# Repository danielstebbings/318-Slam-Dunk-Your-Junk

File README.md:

# SLAM DUNK YOUR JUNK!

This is the full repository for slam dunk your junk, including PCB design files and all source code.

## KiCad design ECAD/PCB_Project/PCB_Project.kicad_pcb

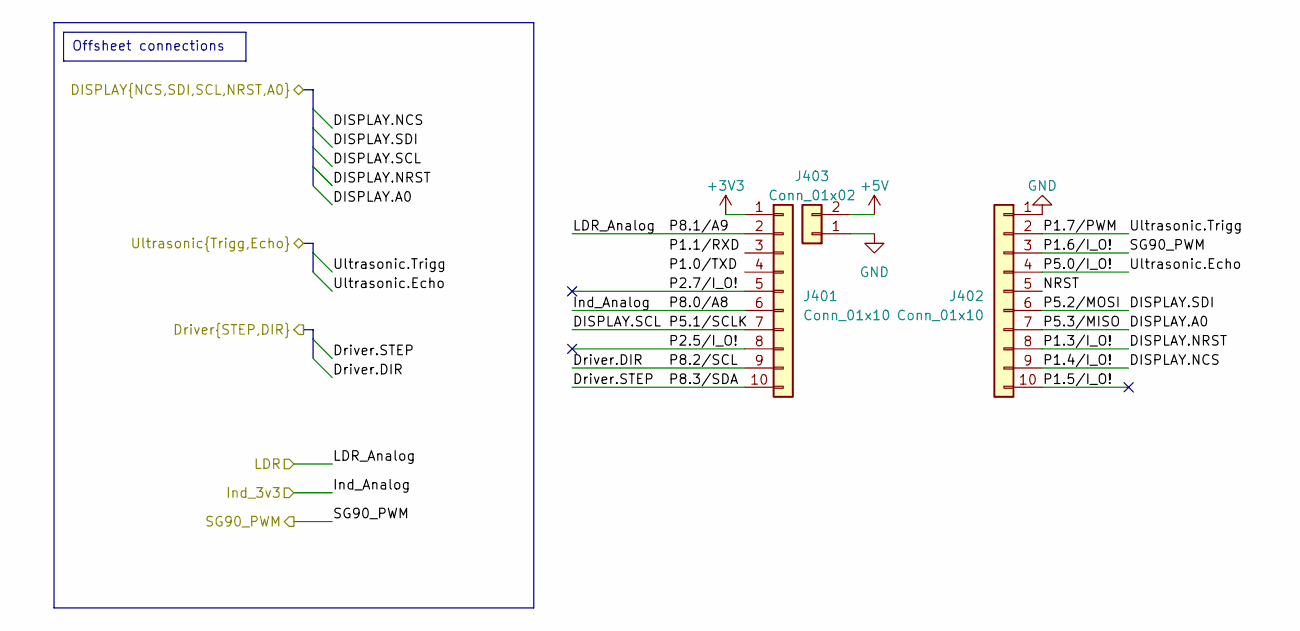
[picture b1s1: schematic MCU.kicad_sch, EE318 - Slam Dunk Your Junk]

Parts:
J401, J402: Conn_01x10; PinSocket_1x10_P2.54mm_Vertical
J403: Conn_01x02; PinHeader_1x02_P2.54mm_Vertical

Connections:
+3V3: J401.1; also elsewhere on the board
+5V: J403.2; also elsewhere on the board
/Display/DISPLAY.A0: J402.7; also elsewhere on the board
/Display/DISPLAY.NCS: J402.9; also elsewhere on the board
/Display/DISPLAY.NRST: J402.8; also elsewhere on the board
/Display/DISPLAY.SCL: J401.7; also elsewhere on the board
/Display/DISPLAY.SDI: J402.6; also elsewhere on the board
/MCU/Driver.DIR: J401.9; also elsewhere on the board
/MCU/Driver.STEP: J401.10; also elsewhere on the board
/MCU/Ind_Analog: J401.6; also elsewhere on the board
/MCU/LDR_Analog: J401.2; also elsewhere on the board
/MCU/NRST: J402.5
/MCU/P1.5/I_O!: J402.10
/MCU/P1.6/I_O!: J402.3; also elsewhere on the board
/MCU/P2.5/I_O!: J401.8
/MCU/P2.7/I_O!: J401.5
/MCU/Ultrasonic.Echo: J402.4; also elsewhere on the board
/MCU/Ultrasonic.Trigg: J402.2; also elsewhere on the board
GND: J402.1, J403.1; also elsewhere on the board

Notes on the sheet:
Offsheet connections

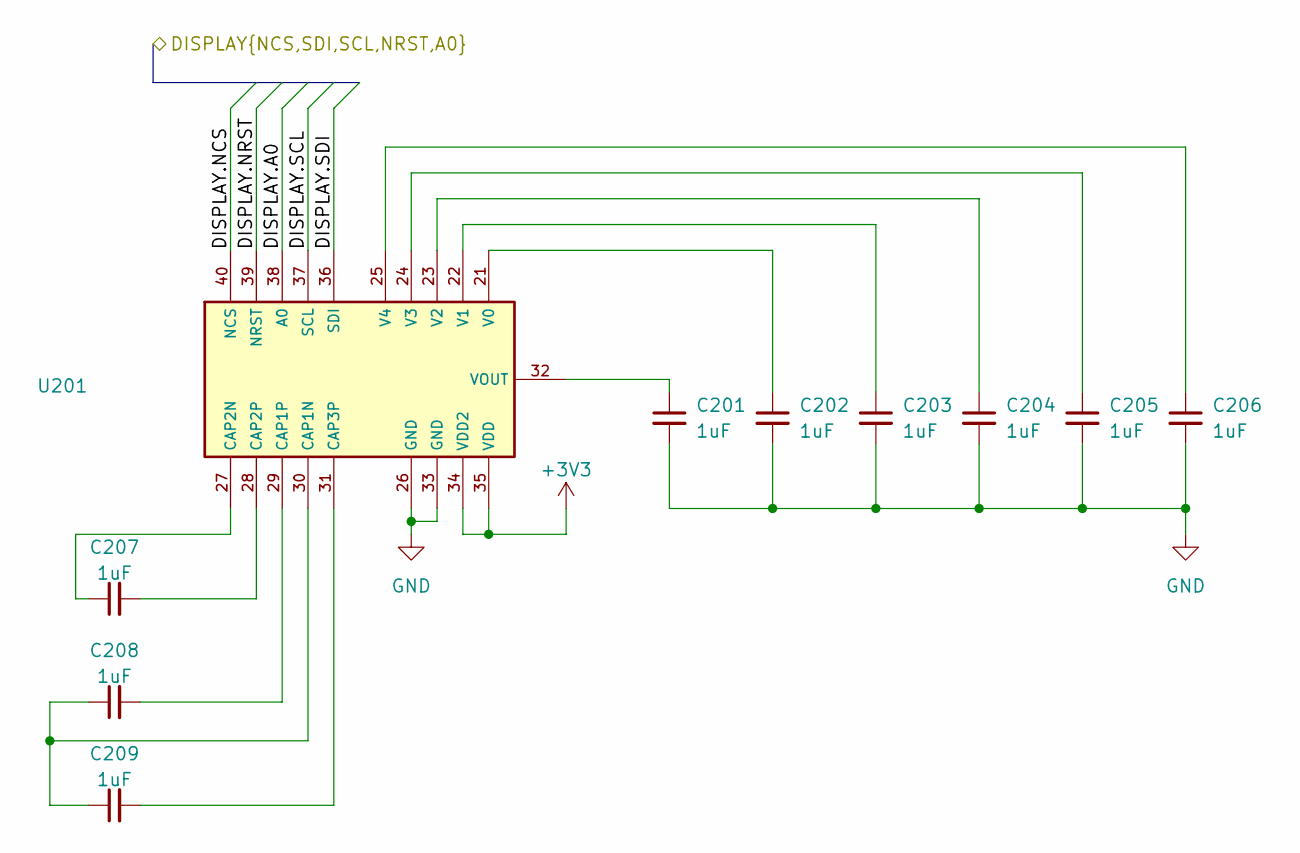
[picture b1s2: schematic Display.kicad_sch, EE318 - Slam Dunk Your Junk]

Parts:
C201, C202, C203, C204, C205, C206, C207, C208, C209: 1uF; C_Disc_D4.3mm_W1.9mm_P5.00mm
U201: EA_DOGL128-6

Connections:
+3V3: U201.34 (VDD2), U201.35 (VDD); also elsewhere on the board
/Display/DISPLAY.A0: U201.38 (A0); also elsewhere on the board
/Display/DISPLAY.NCS: U201.40 (NCS); also elsewhere on the board
/Display/DISPLAY.NRST: U201.39 (NRST); also elsewhere on the board
/Display/DISPLAY.SCL: U201.37 (SCL); also elsewhere on the board
/Display/DISPLAY.SDI: U201.36 (SDI); also elsewhere on the board
GND: C201.2, C202.2, C203.2, C204.2, C205.2, C206.2, U201.26 (GND), U201.33 (GND); also elsewhere on the board
unnamed: C208.1, C209.1, U201.30 (CAP1N)
unnamed: C208.2, U201.29 (CAP1P)
unnamed: C207.1, U201.27 (CAP2N)
unnamed: C207.2, U201.28 (CAP2P)
unnamed: C209.2, U201.31 (CAP3P)
unnamed: C202.1, U201.21 (V0)
unnamed: C203.1, U201.22 (V1)
unnamed: C204.1, U201.23 (V2)
unnamed: C205.1, U201.24 (V3)
unnamed: C206.1, U201.25 (V4)
unnamed: C201.1, U201.32 (VOUT)

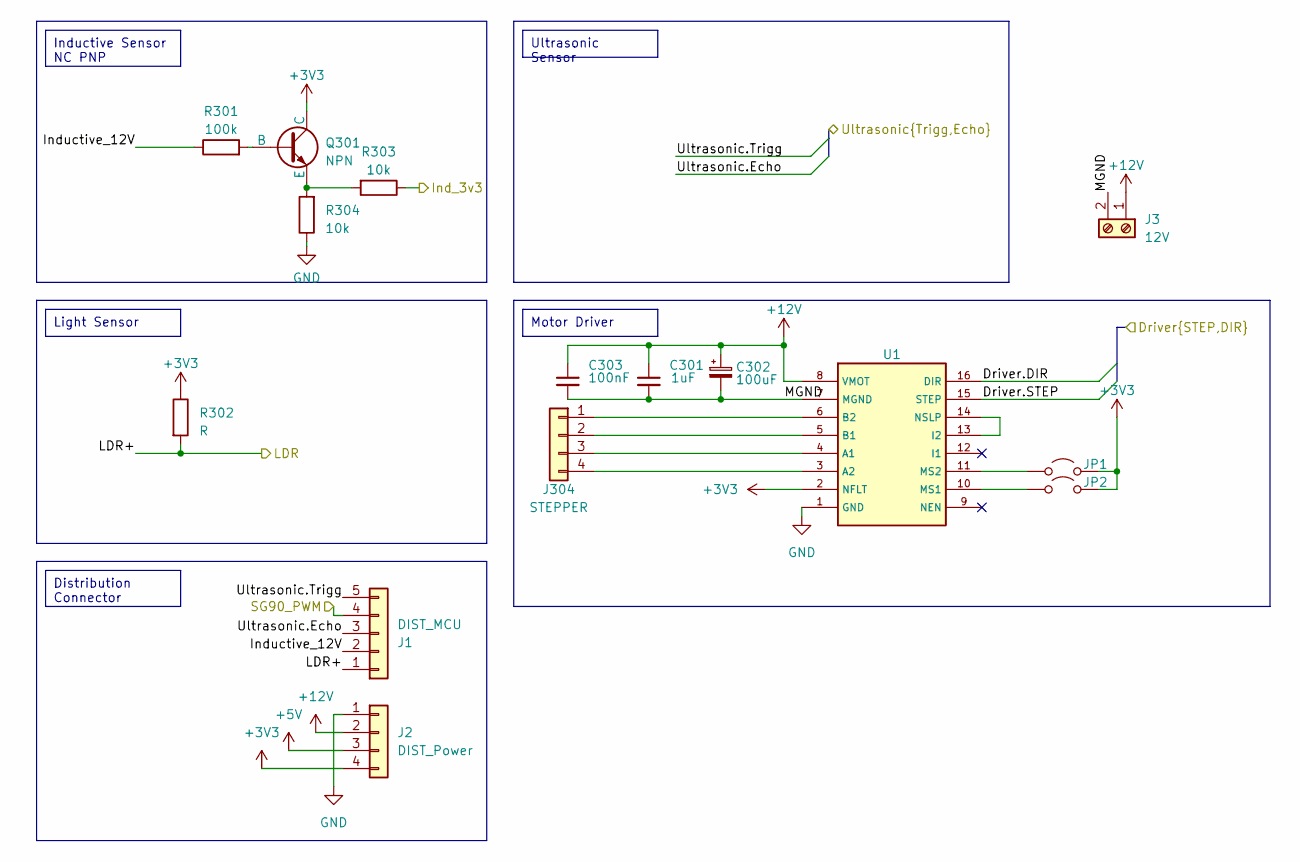
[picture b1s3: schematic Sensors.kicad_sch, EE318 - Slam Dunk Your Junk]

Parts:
C301: 1uF; C_Disc_D4.3mm_W1.9mm_P5.00mm
C302: 100uF; C_Disc_D4.3mm_W1.9mm_P5.00mm
C303: 100nF; C_Disc_D4.3mm_W1.9mm_P5.00mm
J1: DIST_MCU; PinSocket_1x05_P2.54mm_Vertical
J2: DIST_Power; PinHeader_1x04_P2.54mm_Vertical
J3: 12V; TerminalBlock_bornier-2_P5.08mm
J304: STEPPER; TerminalBlock_bornier-4_P5.08mm
JP1, JP2: Jumper_2_Open; R_1206_3216Metric
Q301: NPN; TO-92S_Wide
R301: 100k; R_1206_3216Metric
R302: R; R_1206_3216Metric
R303, R304: 10k; R_1206_3216Metric
U1: MP6500

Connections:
+3V3: J2.4, JP1.2 (B), JP2.2 (B), Q301.1 (C), R302.1, U1.2 (NFLT); also elsewhere on the board
+5V: J2.3; also elsewhere on the board
+12V: C301.1, C302.1, C303.1, J2.2, J3.1, U1.8 (VMOT)
/MCU/Driver.DIR: U1.16 (DIR); also elsewhere on the board
/MCU/Driver.STEP: U1.15 (STEP); also elsewhere on the board
/MCU/Ind_Analog: R303.1; also elsewhere on the board
/MCU/LDR_Analog: J1.1, R302.2; also elsewhere on the board
/MCU/P1.6/I_O!: J1.4; also elsewhere on the board
/MCU/Ultrasonic.Echo: J1.3; also elsewhere on the board
/MCU/Ultrasonic.Trigg: J1.5; also elsewhere on the board
/Sensors + Motor/Inductive_12V: J1.2, R301.1
/Sensors + Motor/MGND: C301.2, C302.2, C303.2, J3.2, U1.7 (MGND)
GND: J2.1, R304.1, U1.1 (GND); also elsewhere on the board
unnamed: J304.1, U1.6 (B2)
unnamed: J304.2, U1.5 (B1)
unnamed: J304.3, U1.4 (A1)
unnamed: J304.4, U1.3 (A2)
unnamed: JP1.1 (A), U1.11 (MS2)
unnamed: JP2.1 (A), U1.10 (MS1)
unnamed: Q301.2 (B), R301.2
unnamed: Q301.3 (E), R303.2, R304.2
unnamed: U1.13 (I2), U1.14 (NSLP)

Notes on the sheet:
Motor Driver
Inductive Sensor NC PNP
Ultrasonic Sensor
Light Sensor
Distribution Connector

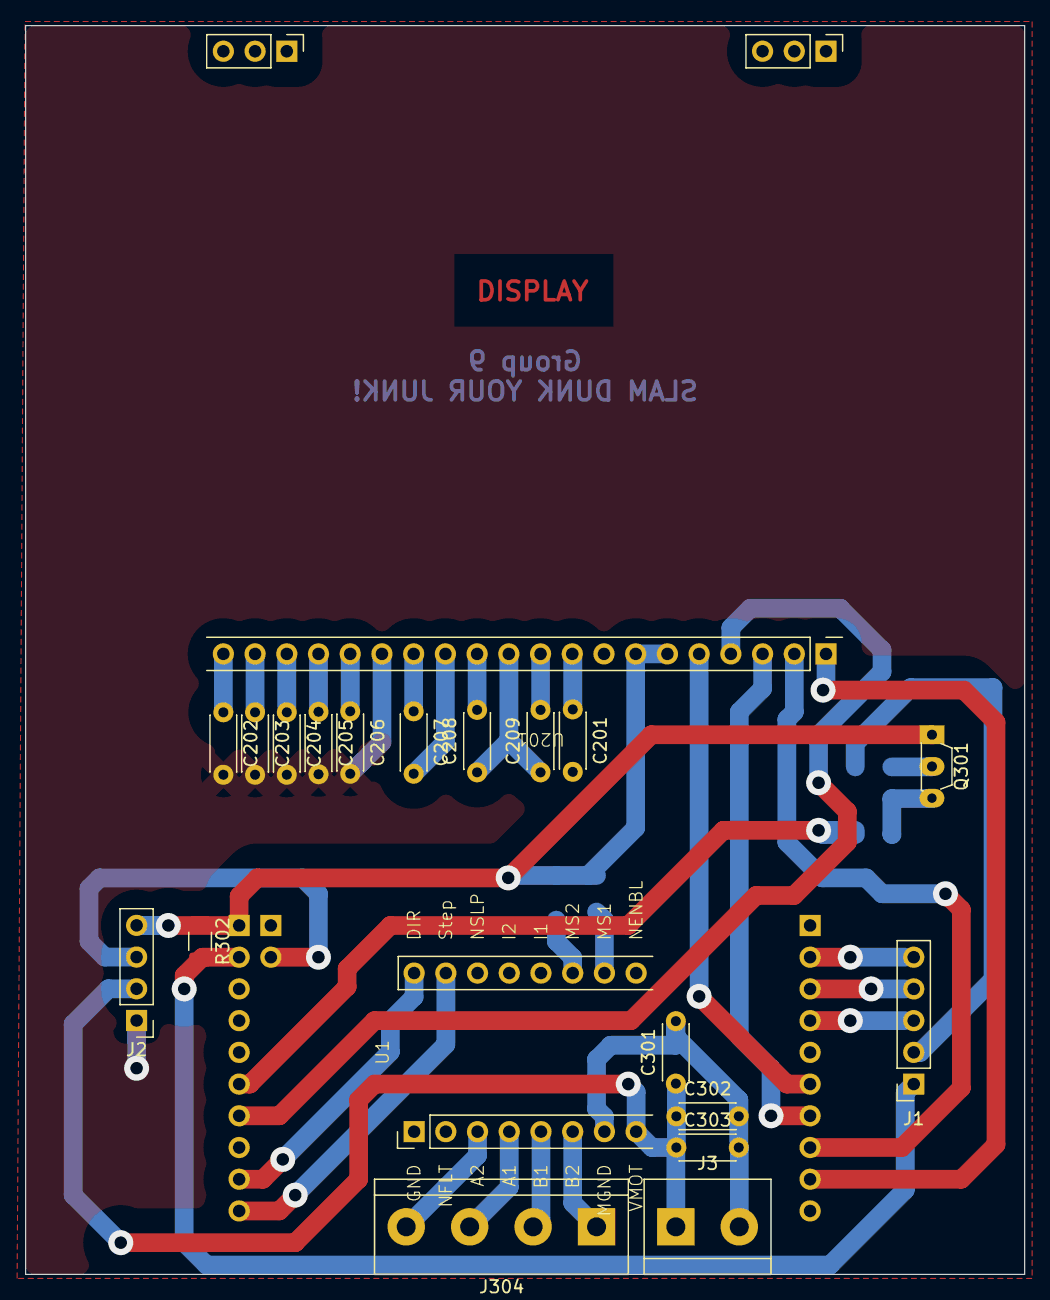
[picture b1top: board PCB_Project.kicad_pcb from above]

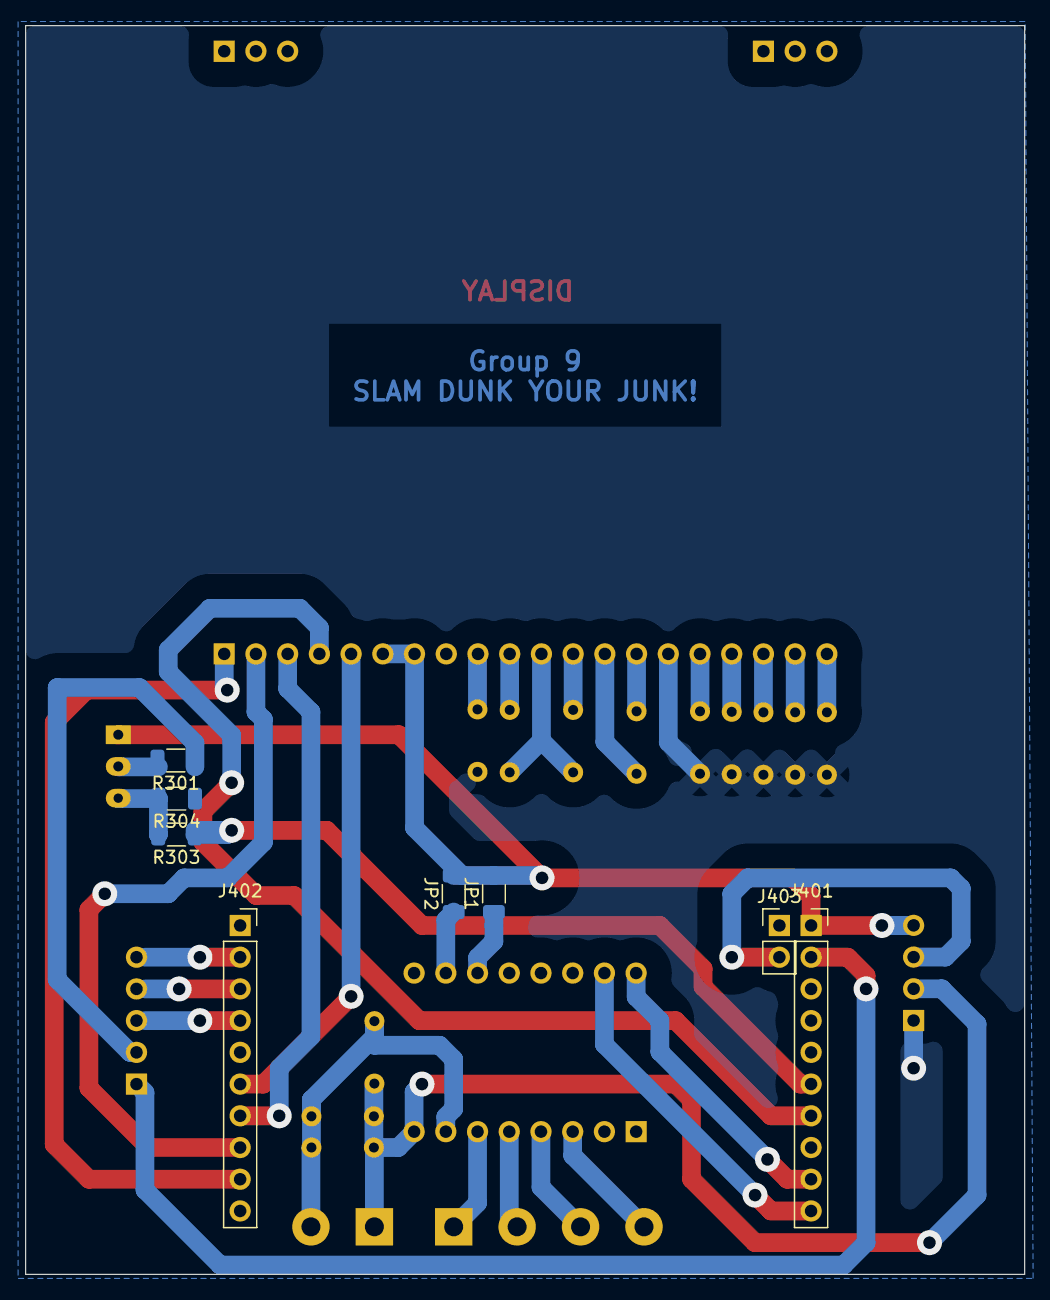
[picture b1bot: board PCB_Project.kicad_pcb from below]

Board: 2 copper layers, 80.0 x 100.0 mm, 28 parts (8 on the bottom side), 38 nets.

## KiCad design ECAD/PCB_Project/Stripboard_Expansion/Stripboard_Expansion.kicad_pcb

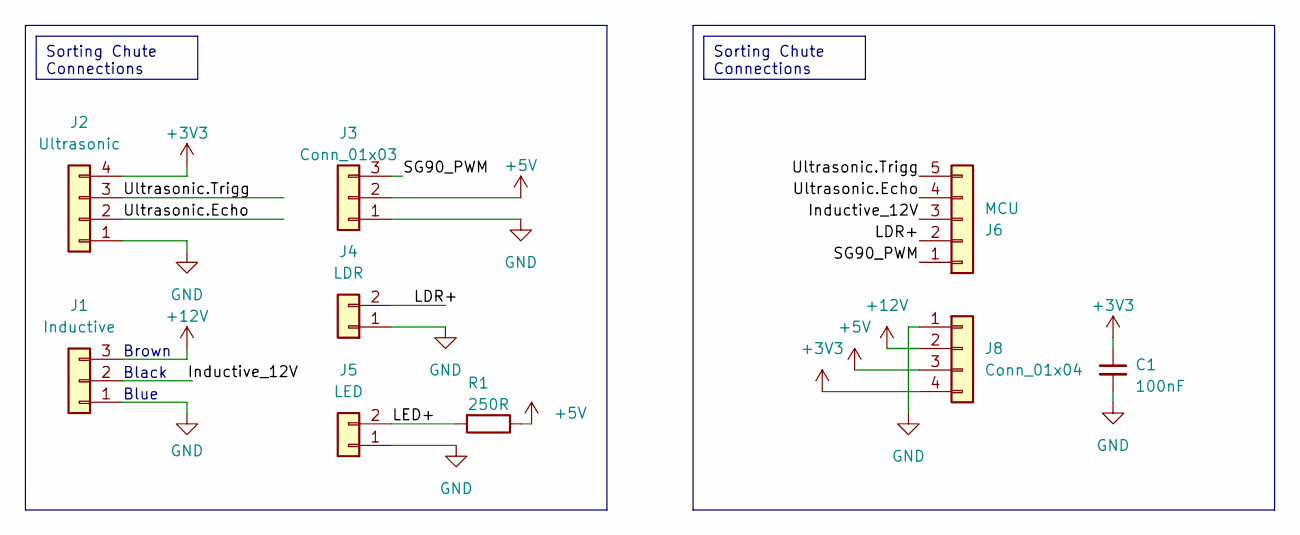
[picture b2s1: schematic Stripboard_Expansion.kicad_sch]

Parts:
C1: 100nF; C_Disc_D4.3mm_W1.9mm_P5.00mm
J1: Inductive; PinHeader_1x03_P2.54mm_Vertical
J2: Ultrasonic; PinHeader_1x04_P2.54mm_Vertical
J3: Conn_01x03; PinHeader_1x03_P2.54mm_Vertical
J4: LDR; PinHeader_1x02_P2.54mm_Vertical
J5: LED; PinHeader_1x02_P2.54mm_Vertical
J6: MCU; PinSocket_1x05_P2.54mm_Vertical
J8: Conn_01x04; PinHeader_1x04_P2.54mm_Vertical
R1: 250R; R_Axial_DIN0204_L3.6mm_D1.6mm_P5.08mm_Vertical

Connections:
+3V3: C1.1, J2.4, J8.4
+5V: J3.2, J8.3, R1.1
+12V: J1.3, J8.2
/Inductive_12V: J1.2, J6.3
/LDR+: J4.2, J6.2
/LED+: J5.2, R1.2
/SG90_PWM: J3.3, J6.1
/Ultrasonic.Echo: J2.2, J6.4
/Ultrasonic.Trigg: J2.3, J6.5
GND: C1.2, J1.1, J2.1, J3.1, J4.1, J5.1, J8.1

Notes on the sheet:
Sorting Chute Connections
Blue
Black
Brown

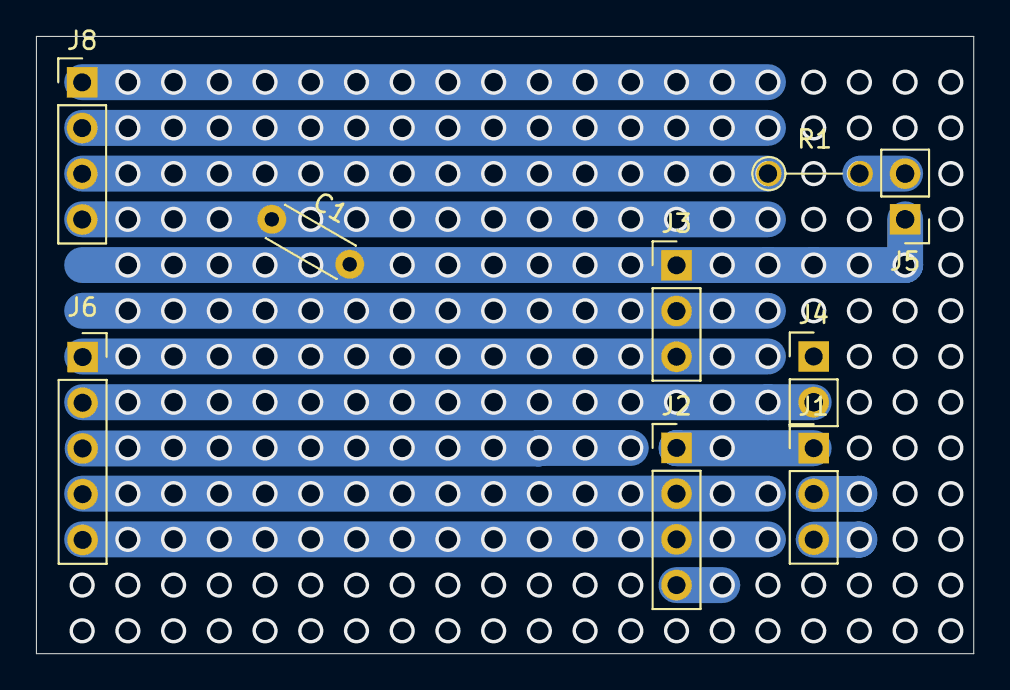
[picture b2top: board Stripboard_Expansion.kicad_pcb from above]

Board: 10 copper layers, 52.1 x 34.3 mm, 9 parts (0 on the bottom side), 10 nets.

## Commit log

2024-02-07 initial
2024-02-07 adding fodlers
2024-02-07 create
2024-02-11 Schematic Creation
    Created KiCAD Project
    Added Inductor Schematic
    Added LDR Schematic (need to choose resistor values)
    Added Motor driver schematic
    Added Display schematic
    Todo: MCU
2024-02-13 Schematic Updates
    Wiring up MCU
    Adding some footprints
2024-02-24 Adding Inductive Sensor Transistor
    Sims + Schematics
2024-02-26 Initial work on motor driver
2024-03-18 Stepper Driver stuff
2024-03-18 Inductive Sensor Transistor Sims
2024-03-18 First PCB Draft
2024-03-21 code update
2024-04-01 PCB Update
2024-04-05 PCB Overhaul
    Stripboard Expansion
    -created
    -schematic
    -routing
    Main PCB
    -Flipped sides to not cover buttons
2024-04-29 Final PCB
2024-05-03 Pushing
    COde changes:
    MP driver under development
    SG90 as well
    PCB:
    final version, as sent to manufacture
    Sims
2024-05-03 final sg90 code
2024-05-03 Final Final
2024-05-03 final
2024-05-08 Update
    Motoring
2024-05-09 Late night editing
2024-05-09 Final code commit
